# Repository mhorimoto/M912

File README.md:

M912
=====

30th March 2021  
M.Horimoto

SOPi装置のフロントパネルに装着するLED用の基板。  
OPiなどの3.3Vの場合には510Ωから1kΩ程度の抵抗で良いと感じる。

実装の向きなどは、3Dグラフィックを参照の上、組み立てる。

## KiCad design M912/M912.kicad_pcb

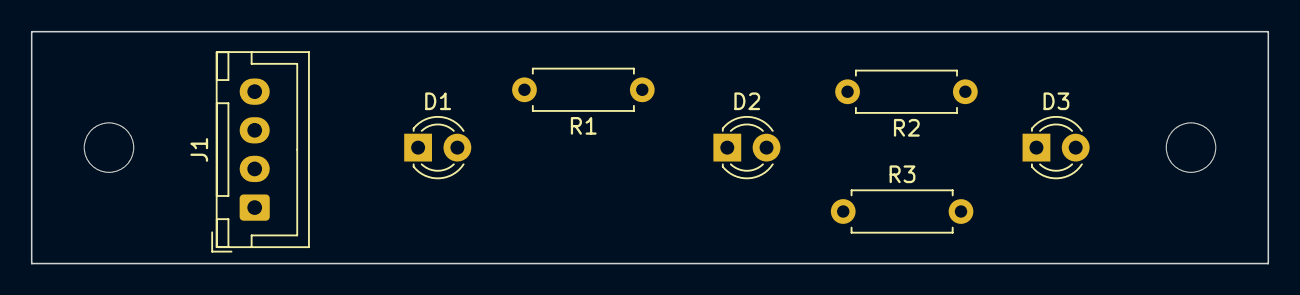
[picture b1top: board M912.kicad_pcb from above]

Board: 2 copper layers, 80.0 x 15.0 mm, 7 parts (0 on the bottom side), 7 nets, no tracks yet.

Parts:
D1, D2, D3: LED; LED_D3.0mm
J1: Conn_01x04; JST_XH_B4B-XH-A_1x04_P2.50mm_Vertical
R1, R2, R3: 1k; R_Axial_DIN0207_L6.3mm_D2.5mm_P7.62mm_Horizontal

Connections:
unnamed: D1.1, J1.1
unnamed: D1.2, R1.2
unnamed: D2.1, J1.2
unnamed: D2.2, R2.2
unnamed: D3.1, J1.3
unnamed: D3.2, R3.2
unnamed: J1.4, R1.1, R2.1, R3.1

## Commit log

2021-03-30 1st Release
2021-03-30 dirs: ディレクトリ構造の見直し変更
2021-04-08 docs: README.mdに追記
